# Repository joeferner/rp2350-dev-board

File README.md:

# RP2350 Dev Board

Minimal RP2350 dev board.

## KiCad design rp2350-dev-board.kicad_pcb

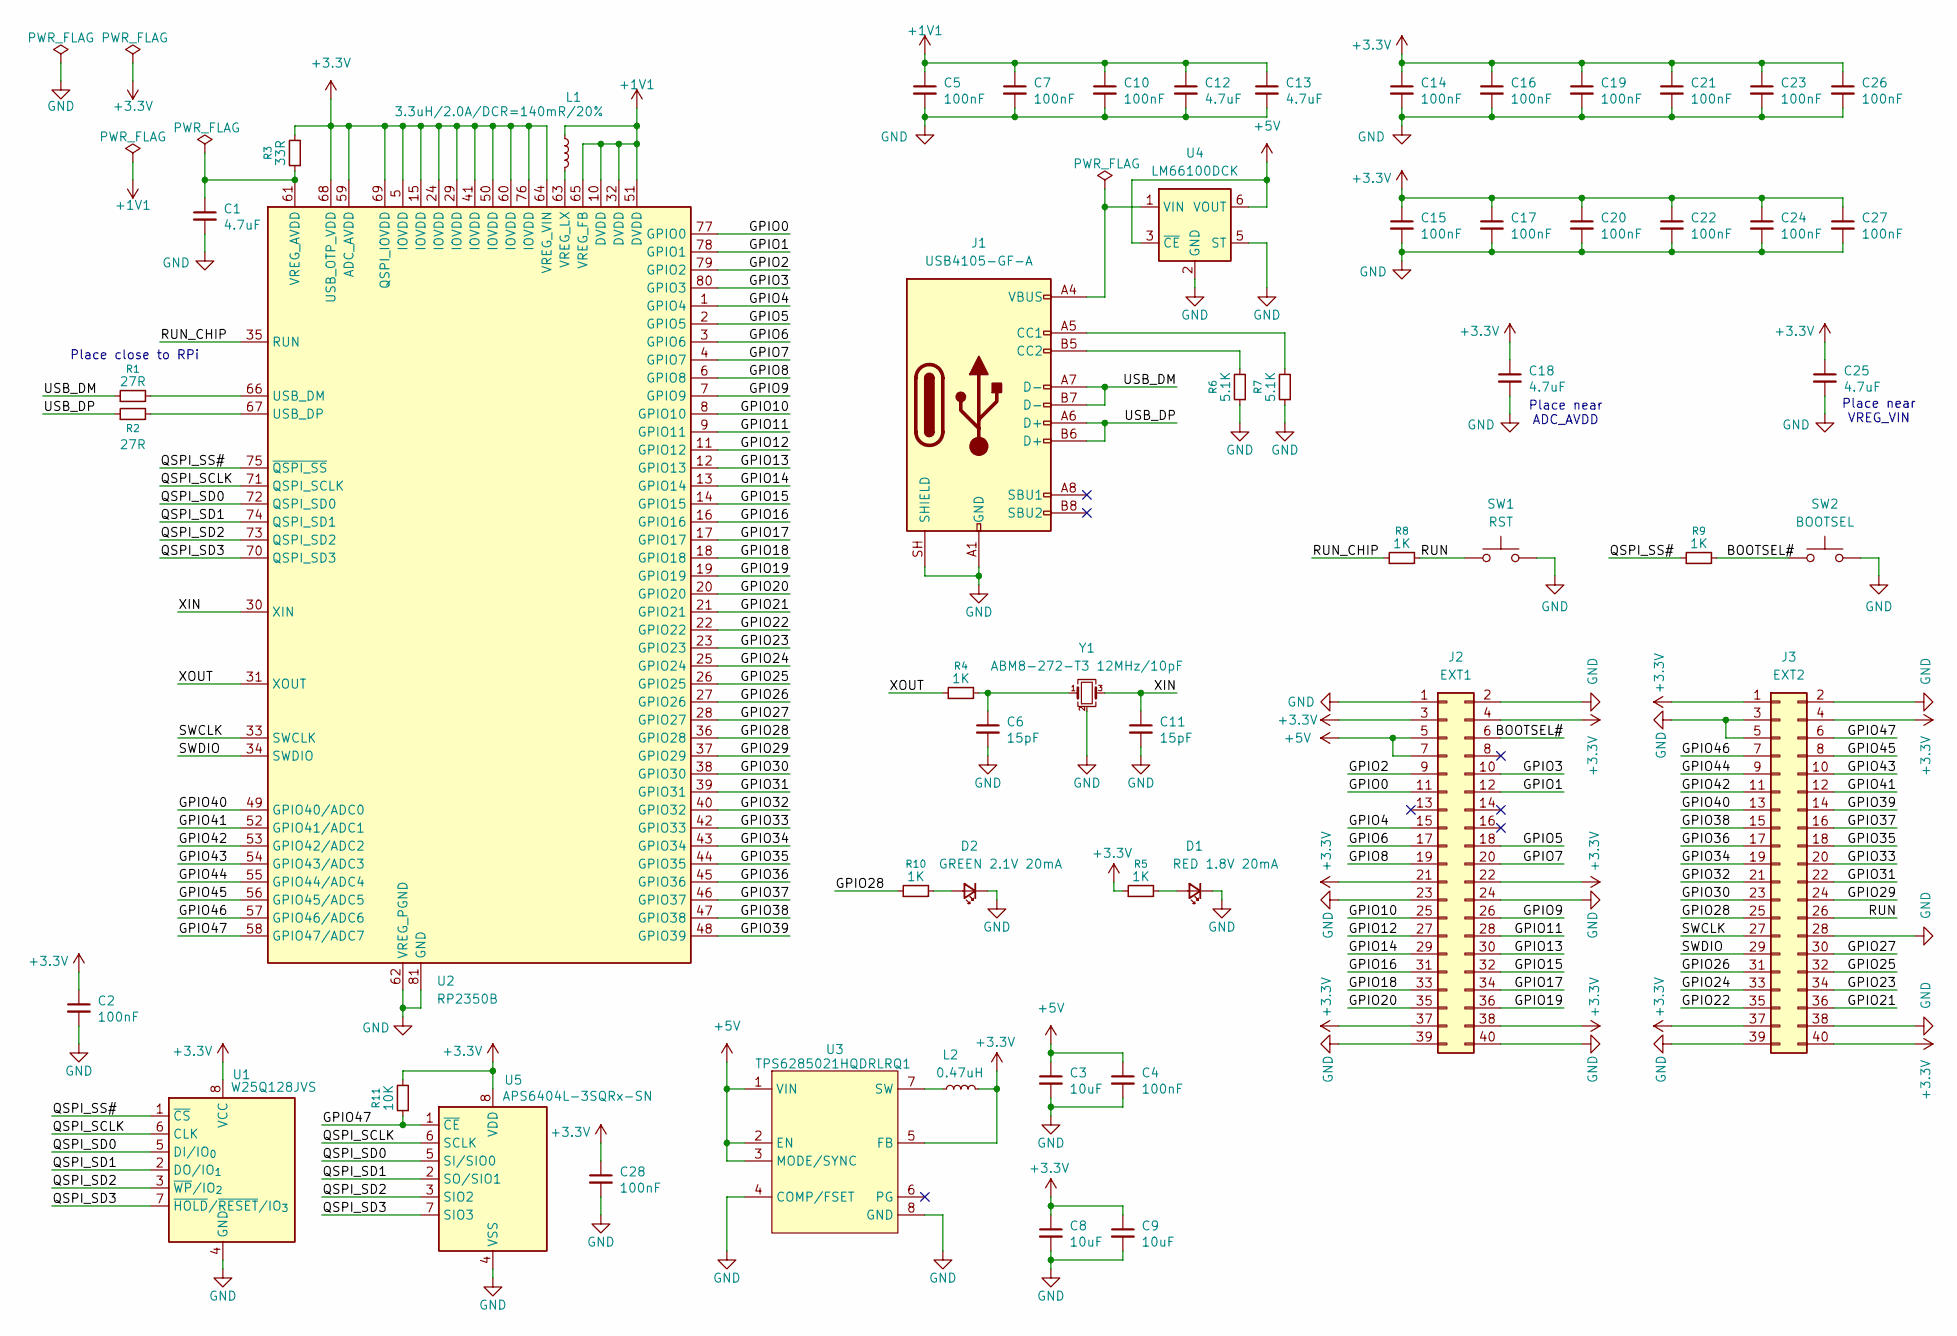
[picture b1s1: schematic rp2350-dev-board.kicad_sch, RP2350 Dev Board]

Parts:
C1, C12, C13, C18, C25: 4.7uF; C_0402_1005Metric_Pad0.74x0.62mm_HandSolder
C2, C4, C5, C7, C10, C14, C15, C16, C17, C19, C20, C21, C22, C23, C24, C26, C27, C28: 100nF; C_0402_1005Metric_Pad0.74x0.62mm_HandSolder
C3, C8, C9: 10uF; C_0805_2012Metric_Pad1.18x1.45mm_HandSolder
C6, C11: 15pF; C_0402_1005Metric_Pad0.74x0.62mm_HandSolder
D1: RED 1.8V 20mA; LED_0805_2012Metric_Pad1.15x1.40mm_HandSolder
D2: GREEN 2.1V 20mA; LED_0805_2012Metric_Pad1.15x1.40mm_HandSolder
J1: USB4105-GF-A; USB_C_Receptacle_GCT_USB4105-xx-A_16P_TopMnt_Horizontal
J2: EXT1; PinHeader_2x20_P2.54mm_Vertical
J3: EXT2; PinHeader_2x20_P2.54mm_Vertical
L1: 3.3uH/2.0A/DCR=140mR/20%; L_Changjiang_FTC201612S
L2: 0.47uH; L_Changjiang_FTC201612S
R1, R2: 27R; R_0402_1005Metric_Pad0.72x0.64mm_HandSolder
R3: 33R; R_0402_1005Metric_Pad0.72x0.64mm_HandSolder
R4: 1K; R_0402_1005Metric_Pad0.72x0.64mm_HandSolder
R5, R8, R9, R10: 1K; R_0805_2012Metric_Pad1.20x1.40mm_HandSolder
R6, R7: 5.1K; R_0805_2012Metric_Pad1.20x1.40mm_HandSolder
R11: 10K; R_0805_2012Metric_Pad1.20x1.40mm_HandSolder
SW1: RST; SW_PUSH_6mm_H5mm
SW2: BOOTSEL; SW_PUSH_6mm_H5mm
U1: W25Q128JVS; SOIC-8_5.3x5.3mm_P1.27mm
U2: RP2350B; QFN-80-1EP_10x10mm_P0.4mm_EP3.4x3.4mm
U3: TPS6285021HQDRLRQ1; SOT-583-8
U4: LM66100DCK; SOT-363_SC-70-6
U5: APS6404L-3SQRx-SN; SOIC-8_3.9x4.9mm_P1.27mm
Y1: ABM8-272-T3 12MHz/10pF; Crystal_SMD_Abracon_ABM8G-4Pin_3.2x2.5mm

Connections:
+1V1: C5.1, C7.1, C10.1, C12.1, C13.1, L1.1, U2.10 (DVDD), U2.32 (DVDD), U2.51 (DVDD), U2.65 (VREG_FB)
+3.3V: C2.1, C8.1, C9.1, C14.1, C15.1, C16.1, C17.1, C18.1, C19.1, C20.1, C21.1, C22.1, C23.1, C24.1, C25.1, C26.1, C27.1, C28.1, J2.3, J2.4, J2.21, J2.22, J2.37, J2.38, J3.1, J3.4, J3.37, J3.40, L2.2, R3.2, R5.1, R11.2, U1.8 (VCC), U2.5 (IOVDD), U2.15 (IOVDD), U2.24 (IOVDD), U2.29 (IOVDD), U2.41 (IOVDD), U2.50 (IOVDD), U2.59 (ADC_AVDD), U2.60 (IOVDD), U2.64 (VREG_VIN), U2.68 (USB_OTP_VDD), U2.69 (QSPI_IOVDD), U2.76 (IOVDD), U3.5 (FB), U5.8 (VDD)
+5V: C3.1, C4.1, J2.5, J2.7, U3.1 (VIN), U3.2 (EN), U3.3 (MODE/SYNC), U4.3 (~CE), U4.6 (VOUT)
/BOOTSEL#: J2.6, R9.2, SW2.1
/GPIO0: J2.11, U2.77 (GPIO0)
/GPIO1: J2.12, U2.78 (GPIO1)
/GPIO2: J2.9, U2.79 (GPIO2)
/GPIO3: J2.10, U2.80 (GPIO3)
/GPIO4: J2.15, U2.1 (GPIO4)
/GPIO5: J2.18, U2.2 (GPIO5)
/GPIO6: J2.17, U2.3 (GPIO6)
/GPIO7: J2.20, U2.4 (GPIO7)
/GPIO8: J2.19, U2.6 (GPIO8)
/GPIO9: J2.26, U2.7 (GPIO9)
/GPIO10: J2.25, U2.8 (GPIO10)
/GPIO11: J2.28, U2.9 (GPIO11)
/GPIO12: J2.27, U2.11 (GPIO12)
/GPIO13: J2.30, U2.12 (GPIO13)
/GPIO14: J2.29, U2.13 (GPIO14)
/GPIO15: J2.32, U2.14 (GPIO15)
/GPIO16: J2.31, U2.16 (GPIO16)
/GPIO17: J2.34, U2.17 (GPIO17)
/GPIO18: J2.33, U2.18 (GPIO18)
/GPIO19: J2.36, U2.19 (GPIO19)
/GPIO20: J2.35, U2.20 (GPIO20)
/GPIO21: J3.36, U2.21 (GPIO21)
/GPIO22: J3.35, U2.22 (GPIO22)
/GPIO23: J3.34, U2.23 (GPIO23)
/GPIO24: J3.33, U2.25 (GPIO24)
/GPIO25: J3.32, U2.26 (GPIO25)
/GPIO26: J3.31, U2.27 (GPIO26)
/GPIO27: J3.30, U2.28 (GPIO27)
/GPIO28: J3.25, R10.1, U2.36 (GPIO28)
/GPIO29: J3.24, U2.37 (GPIO29)
/GPIO30: J3.23, U2.38 (GPIO30)
/GPIO31: J3.22, U2.39 (GPIO31)
/GPIO32: J3.21, U2.40 (GPIO32)
/GPIO33: J3.20, U2.42 (GPIO33)
/GPIO34: J3.19, U2.43 (GPIO34)
/GPIO35: J3.18, U2.44 (GPIO35)
/GPIO36: J3.17, U2.45 (GPIO36)
/GPIO37: J3.16, U2.46 (GPIO37)
/GPIO38: J3.15, U2.47 (GPIO38)
/GPIO39: J3.14, U2.48 (GPIO39)
/GPIO40: J3.13, U2.49 (GPIO40/ADC0)
/GPIO41: J3.12, U2.52 (GPIO41/ADC1)
/GPIO42: J3.11, U2.53 (GPIO42/ADC2)
/GPIO43: J3.10, U2.54 (GPIO43/ADC3)
/GPIO44: J3.9, U2.55 (GPIO44/ADC4)
/GPIO45: J3.8, U2.56 (GPIO45/ADC5)
/GPIO46: J3.7, U2.57 (GPIO46/ADC6)
/GPIO47: J3.6, R11.1, U2.58 (GPIO47/ADC7), U5.1 (~CE)
/QSPI_SCLK: U1.6 (CLK), U2.71 (QSPI_SCLK), U5.6 (SCLK)
/QSPI_SD0: U1.5 (DI/IO_{0}), U2.72 (QSPI_SD0), U5.5 (SI/SIO0)
/QSPI_SD1: U1.2 (DO/IO_{1}), U2.74 (QSPI_SD1), U5.2 (SO/SIO1)
/QSPI_SD2: U1.3 (~WP/IO_{2}), U2.73 (QSPI_SD2), U5.3 (SIO2)
/QSPI_SD3: U1.7 (~HOLD/~RESET/IO_{3}), U2.70 (QSPI_SD3), U5.7 (SIO3)
/QSPI_SS#: R9.1, U1.1 (~CS), U2.75 (~QSPI_SS)
/RUN: J3.26, R8.2, SW1.1
/RUN_CHIP: R8.1, U2.35 (RUN)
/SWCLK: J3.27, U2.33 (SWCLK)
/SWDIO: J3.29, U2.34 (SWDIO)
/USB_DM: J1.A7 (D-), J1.B7 (D-), R1.1
/USB_DP: J1.A6 (D+), J1.B6 (D+), R2.1
/XIN: C11.1, U2.30 (XIN), Y1.3
/XOUT: R4.1, U2.31 (XOUT)
GND: C1.2, C2.2, C3.2, C4.2, C5.2, C6.2, C7.2, C8.2, C9.2, C10.2, C11.2, C12.2, C13.2, C14.2, C15.2, C16.2, C17.2, C18.2, C19.2, C20.2, C21.2, C22.2, C23.2, C24.2, C25.2, C26.2, C27.2, C28.2, D1.1 (K), D2.1 (K), J1.A1 (GND), J1.A12 (GND), J1.B1 (GND), J1.B12 (GND), J1.SH (SHIELD), J2.1, J2.2, J2.23, J2.24, J2.39, J2.40, J3.2, J3.3, J3.5, J3.28, J3.38, J3.39, R6.1, R7.1, SW1.2, SW2.2, U1.4 (GND), U2.62 (VREG_PGND), U2.81 (GND), U3.4 (COMP/FSET), U3.8 (GND), U4.2 (GND), U4.5 (ST), U5.4 (VSS), Y1.2 (G), Y1.4 (G)
unnamed: C6.1, R4.2, Y1.1
unnamed: D1.2 (A), R5.2
unnamed: D2.2 (A), R10.2
unnamed: J1.A5 (CC1), R7.2
unnamed: J1.B5 (CC2), R6.2
unnamed: R1.2, U2.66 (USB_DM)
unnamed: R2.2, U2.67 (USB_DP)
unnamed: C1.1, R3.1, U2.61 (VREG_AVDD)
unnamed: L1.2, U2.63 (VREG_LX)
unnamed: L2.1, U3.7 (SW)
unnamed: J1.A4 (VBUS), J1.A9 (VBUS), J1.B4 (VBUS), J1.B9 (VBUS), U4.1 (VIN)

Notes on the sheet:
Place near VREG_VIN
Place near ADC_AVDD
Place close to RPi

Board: 2 copper layers, 54 parts (3 on the bottom side), 78 nets, no tracks yet.
